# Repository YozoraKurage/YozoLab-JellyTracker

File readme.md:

# Yozolab-JellyTracker

### ✨️現在作成中です！✨️

私の作った[SlimeVR](https://github.com/SlimeVR)トラッカーに関するリポジトリです。

## FW書き込みについて(書き途中です)
JellyTrackerを私から購入した場合、WebページからFWの更新ができます \
https://jt-webflash.yozolab.net/

## 動作確認済みデータ
- [x] JellyTracker_V0.2.0
- [x] JellyTracker_V0.5.0
- [x] LSM_Module_V0.1.0
- [x] Ni-MH_3.3V-Module_V0.1.0

## KiCADデータについて
(今のところ)すべてKiCAD 7.0で作成されています\
私の導入しているプラグイン
- Espressif Library
- KiCAD JLCPCB tools

## JT_V0.5.0

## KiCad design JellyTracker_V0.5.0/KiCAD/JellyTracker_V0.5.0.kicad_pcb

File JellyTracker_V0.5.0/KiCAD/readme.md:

# JellyTracker_V0.5.0 KiCADデータ

> [!NOTE]
> このKiCADデータはKiCAD V7.0で作成されました！

AUXトラッカーとして、LSM_Module-V0.1.0が利用可能です
> LSM_ModuleとNi-MH_3.3V-Moduleを利用してNi-MH一本での運用が可能です。\
> JT_V0.5.0はそのために作成されました

## How to Upload to JLCPCB
jlcpcb/production_filesに出力されたBOM、CPL、GERBERデータがあるので、それを使うかKiCADからデータを作成してください

## Parts list

| What's it? | Parts Name | LCSC No. |
| ---- | ---- | ---- |
| TypeC Connector | TYPE-C-31-M-12 | C165948 |
| ESP32C3 Module | ESP32-C3-WROOM-02-N4 | C2934560 |
| 3.3V Regulator | ME6211C33M5G-N | C82942 |
| PushButton | SKRKAEE020 | C115357 |
| Caps | CL21B105KBFNNNE | C28323 |
| Resistor | 0603WAF5101T5E  | C23186 |
| Resistor | 0603WAF1002T5E  | C25804 |
| Diode | CUS10S30,H3F | C146335 |
| PH 2.0 | PH-4P | C50137 |

> [!IMPORTANT]
> 私のPH2.0ケーブルでは、必ず **SameSide** のケーブルを使う必要があります！

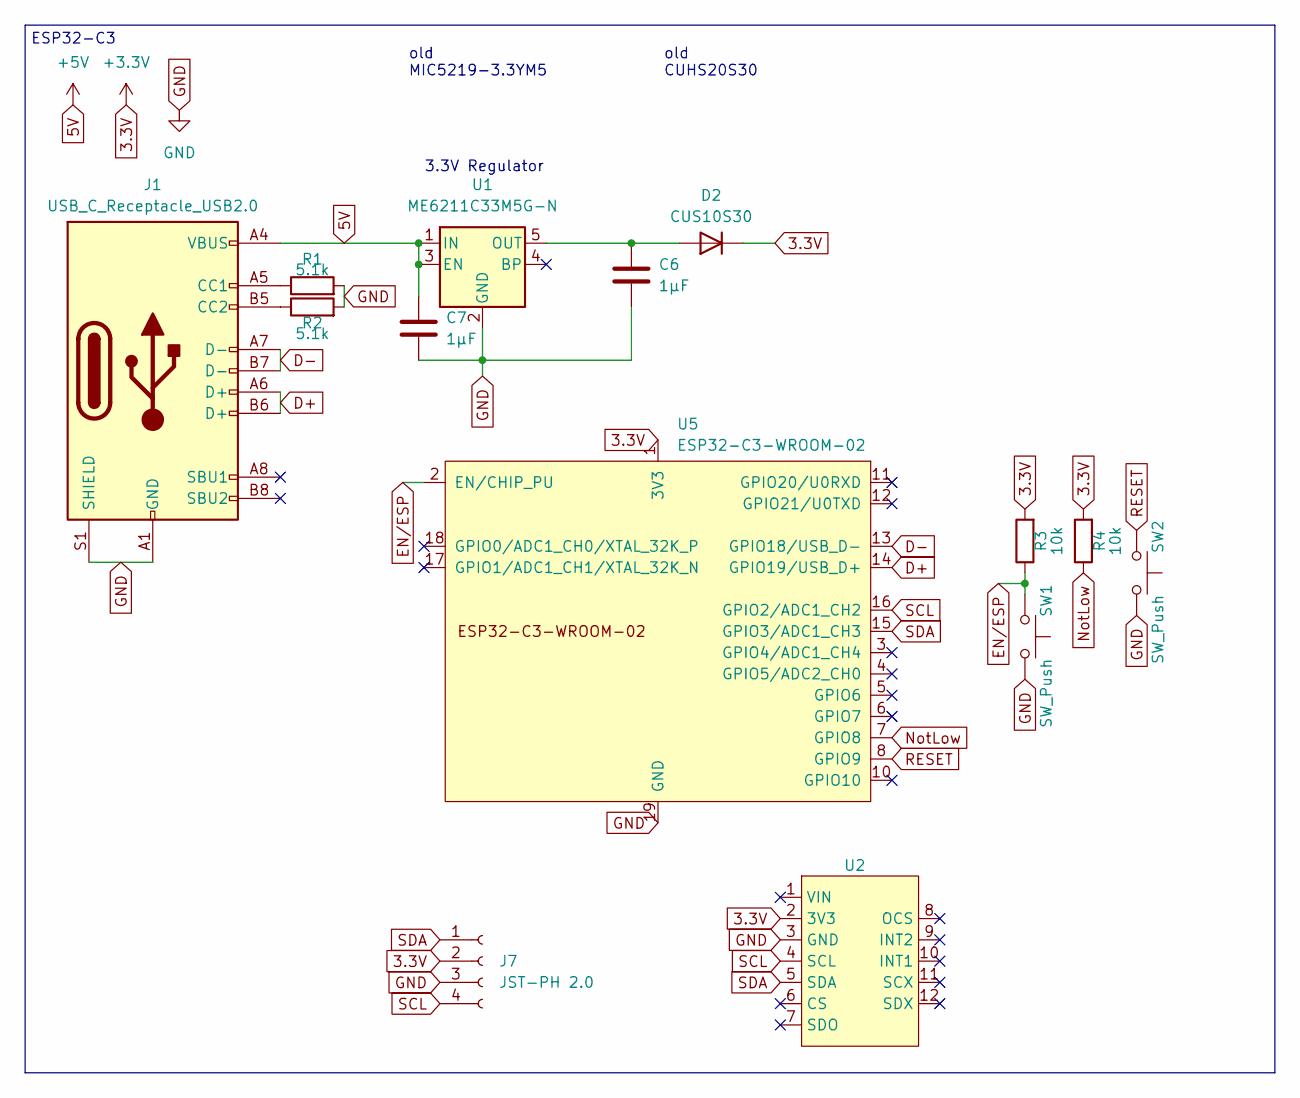
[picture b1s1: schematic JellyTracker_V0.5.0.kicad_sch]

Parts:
C6, C7: 1μF; C_0805_2012Metric
D2: CUS10S30; D_SOD-323
J1: USB_C_Receptacle_USB2.0; USB_C_Receptacle_HRO_TYPE-C-31-M-12
J7: JST-PH 2.0; JST_PH_S4B-PH-SM4-TB_1x04-1MP_P2.00mm_Horizontal
R1, R2: 5.1k; R_0603_1608Metric
R3, R4: 10k; R_0603_1608Metric
SW1, SW2: SW_Push; SW_Push_SPST_NO_Alps_SKRK
U1: ME6211C33M5G-N; SOT-23-5
U2: BMI160-Module
U5: ESP32-C3-WROOM-02

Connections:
3.3V: D2.1 (K), J7.2, R3.2, R4.2, U2.2 (3V3), U5.1 (3V3)
5V: C7.2, J1.A4 (VBUS), J1.A9 (VBUS), J1.B4 (VBUS), J1.B9 (VBUS), U1.1 (IN), U1.3 (EN)
D+: J1.A6 (D+), J1.B6 (D+), U5.14 (GPIO19/USB_D+)
D-: J1.A7 (D-), J1.B7 (D-), U5.13 (GPIO18/USB_D-)
EN/ESP: R3.1, SW1.1, U5.2 (EN/CHIP_PU)
GND: C6.2, C7.1, J1.A1 (GND), J1.A12 (GND), J1.B1 (GND), J1.B12 (GND), J1.S1 (SHIELD), J7.3, R1.2, R2.2, SW1.2, SW2.2, U1.2 (GND), U2.3 (GND), U5.9 (GND), U5.19 (GND)
unnamed: C6.1, D2.2 (A), U1.5 (OUT)
unnamed: J1.A5 (CC1), R1.1
unnamed: J1.B5 (CC2), R2.1
NotLow: R4.1, U5.7 (GPIO8)
RESET: SW2.1, U5.8 (GPIO9)
SCL: J7.4, U2.4 (SCL), U5.16 (GPIO2/ADC1_CH2)
SDA: J7.1, U2.5 (SDA), U5.15 (GPIO3/ADC1_CH3)

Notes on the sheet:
ESP32-C3
old CUHS20S30
3.3V Regulator
old MIC5219-3.3YM5

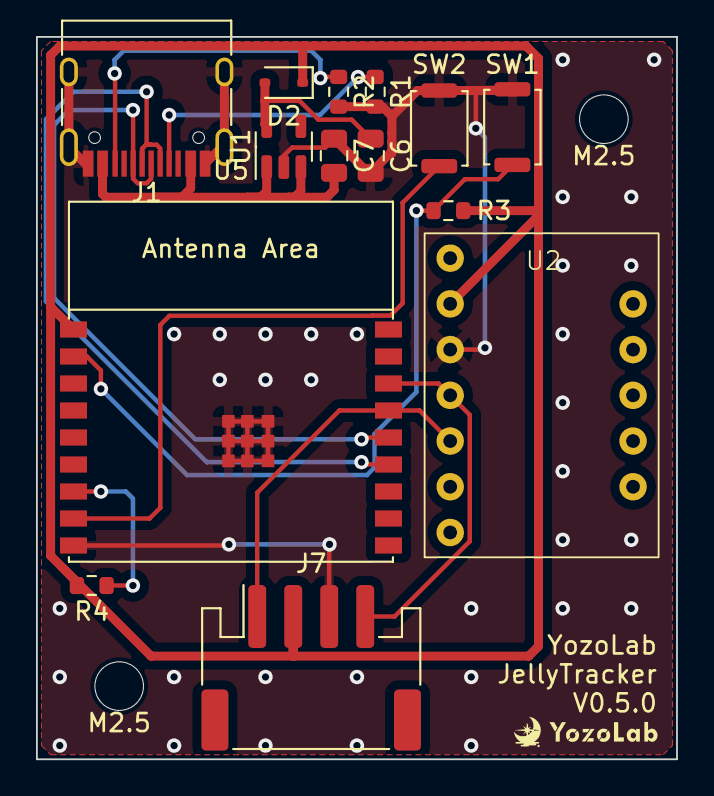
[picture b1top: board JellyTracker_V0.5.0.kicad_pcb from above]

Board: 2 copper layers, 35.6 x 40.1 mm, 16 parts (0 on the bottom side), 13 nets.

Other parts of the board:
M2.5, M2.5#2: MountingHole_2.7mm_M2.5

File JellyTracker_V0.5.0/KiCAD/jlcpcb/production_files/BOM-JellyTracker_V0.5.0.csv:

Comment,Designator,Footprint,LCSC,Quantity
SW_Push,"SW1,SW2",SW_Push_SPST_NO_Alps_SKRK,C115357,2
"CUS10S30
",D2,D_SOD-323,C146335,1
USB_C_Receptacle_USB2.0,J1,USB_C_Receptacle_HRO_TYPE-C-31-M-12,C165948,1
5.1k,"R1,R2",R_0603_1608Metric,C23186,2
10k,"R3,R4",R_0603_1608Metric,C25804,2
1μF,"C6,C7",C_0805_2012Metric,C28323,2
ESP32-C3-WROOM-02,U5,ESP32-C3-WROOM-02,C2934560,1
JST-PH 2.0,J7,JST_PH_S4B-PH-SM4-TB_1x04-1MP_P2.00mm_Horizontal,C50137,1
ME6211C33M5G-N,U1,SOT-23-5,C82942,1

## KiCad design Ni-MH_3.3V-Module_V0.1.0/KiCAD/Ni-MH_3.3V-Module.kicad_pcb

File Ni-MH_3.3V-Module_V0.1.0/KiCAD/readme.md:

# NiMH 3.3V昇圧モジュール KiCADデータ
Ni-MHを3.3Vへ昇圧するモジュールです。

## How to Upload to JLCPCB
jlcpcb/production_filesに出力されたBOM、CPL、GERBERデータがあるので、それを使うかKiCADからデータを作成してください

## Parts list
| What's it? | Parts Name | LCSC No. |
| ---- | ---- | ---- |
| Caps | CL10C100JB8NNNC | C1634 |
| Inductor | DFE252012P-R47M=P2 | C237552 |
| Resistor | 0603WAF3163T5E | C25814 |
| 1.2v to 3.3v DCDC | TPS61021ADSGR | C193037 |
| Caps | CL21A226MAQNNNE  | C45783 |
| Resistor | 0603WAF1003T5E | C25803 |
| Diode | CUS10S30,H3F | C146335 |

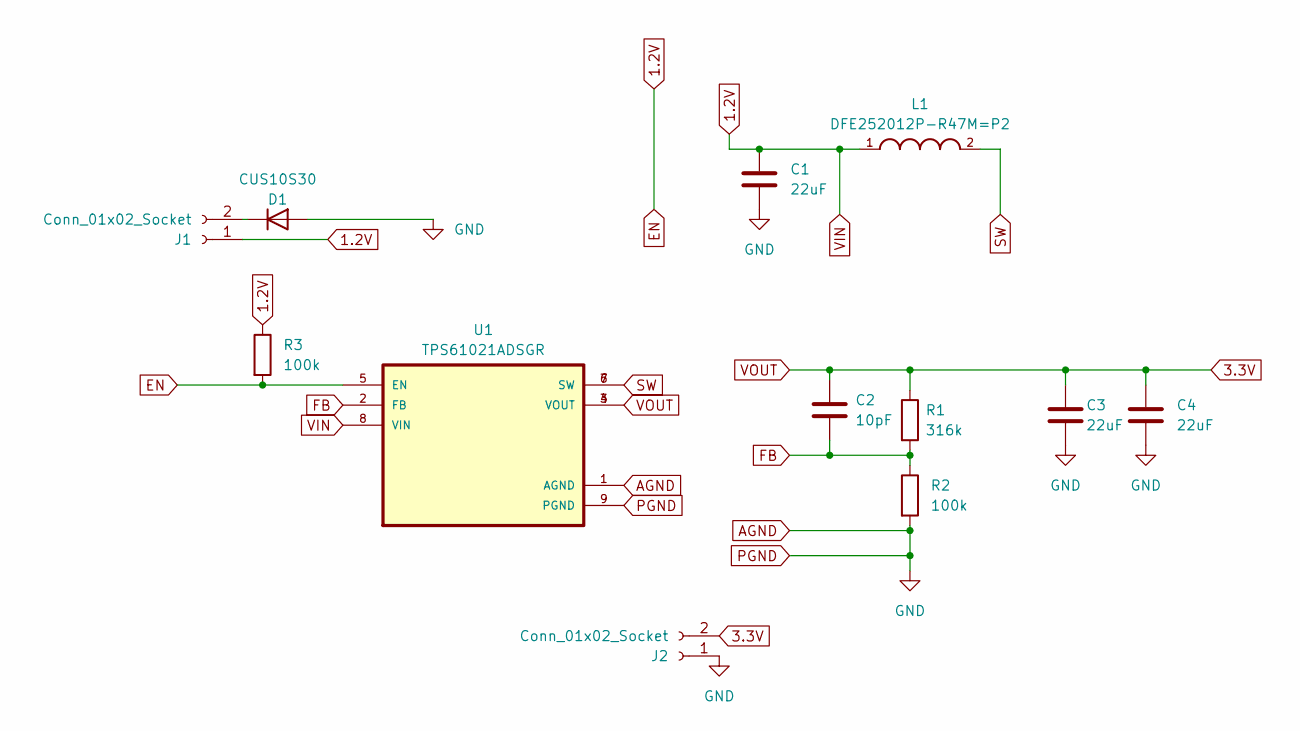
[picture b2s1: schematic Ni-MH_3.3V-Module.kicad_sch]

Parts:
C1, C3, C4: 22uF; C_0805_2012Metric
C2: 10pF; C_0603_1608Metric
D1: CUS10S30; D_SOD-323
J1, J2: Conn_01x02_Socket; Through-Hole
L1: DFE252012P-R47M=P2; INDC2520X120N
R1: 316k; R_0603_1608Metric
R2, R3: 100k; R_0603_1608Metric
U1: TPS61021ADSGR; SON50P200X200X80-9N

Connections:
1.2V: C1.2, J1.1, L1.1, R3.1, R3.2, U1.5 (EN), U1.8 (VIN)
3.3V: C2.2, C3.2, C4.2, J2.2, R1.1, U1.3 (VOUT), U1.4 (VOUT)
AGND: C1.1, C3.1, C4.1, D1.2 (A), J2.1, R2.2, U1.1 (AGND), U1.9 (PGND)
FB: C2.1, R1.2, R2.1, U1.2 (FB)
unnamed: D1.1 (K), J1.2
SW: L1.2, U1.6 (SW), U1.7 (SW)

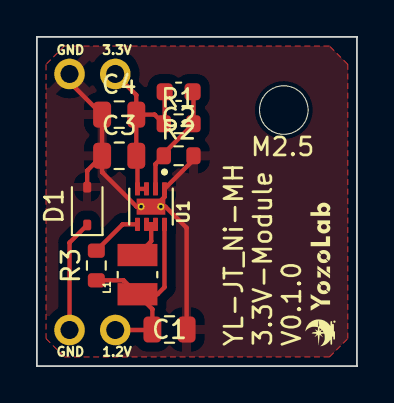
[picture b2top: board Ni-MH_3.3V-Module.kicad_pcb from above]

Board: 2 copper layers, 17.8 x 18.3 mm, 13 parts (0 on the bottom side), 6 nets.

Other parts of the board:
M2.5: MountingHole_2.7mm_M2.5

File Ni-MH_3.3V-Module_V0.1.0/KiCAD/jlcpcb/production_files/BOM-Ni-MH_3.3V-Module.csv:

Comment,Designator,Footprint,LCSC,Quantity
CUS10S30,D1,D_SOD-323,C146335,1
10pF,C2,C_0603_1608Metric,C1634,1
TPS61021ADSGR,U1,SON50P200X200X80-9N,C193037,1
DFE252012P-R47M=P2,L1,INDC2520X120N,C237552,1
100k,"R2,R3",R_0603_1608Metric,C25803,2
316k,R1,R_0603_1608Metric,C25814,1
22uF,"C1,C3,C4",C_0805_2012Metric,C45783,3

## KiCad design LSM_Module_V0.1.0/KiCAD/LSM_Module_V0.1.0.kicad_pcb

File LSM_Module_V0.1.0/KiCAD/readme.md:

# LSM_Module_V0.1.0 KiCADデータ

LSM6シリーズ、及びBMIシリーズのモジュールにコネクタを付けてAUXトラッカーとして扱うための基板データです。

白猫屋さんのこのLSM6DSVモジュールでの動作を確認済みです。\
https://booth.pm/ja/items/5606882

## How to Upload to JLCPCB
jlcpcb/production_filesに出力されたBOM、CPL、GERBERデータがあるので、それを使うかKiCADからデータを作成してください

## Parts list
| Parts Name | LCSC No. |
| ---- | ---- |
| PH2.0mm 4pin | C50137 or https://www.aliexpress.com/item/1005006027334406.html |
| PH2.0mm 4pin-wire **SameSide** | https://ja.aliexpress.com/item/1005003395992629.html |

> [!IMPORTANT]
> 私のPH2.0ケーブルでは、必ず **SameSide** のケーブルを使う必要があります！

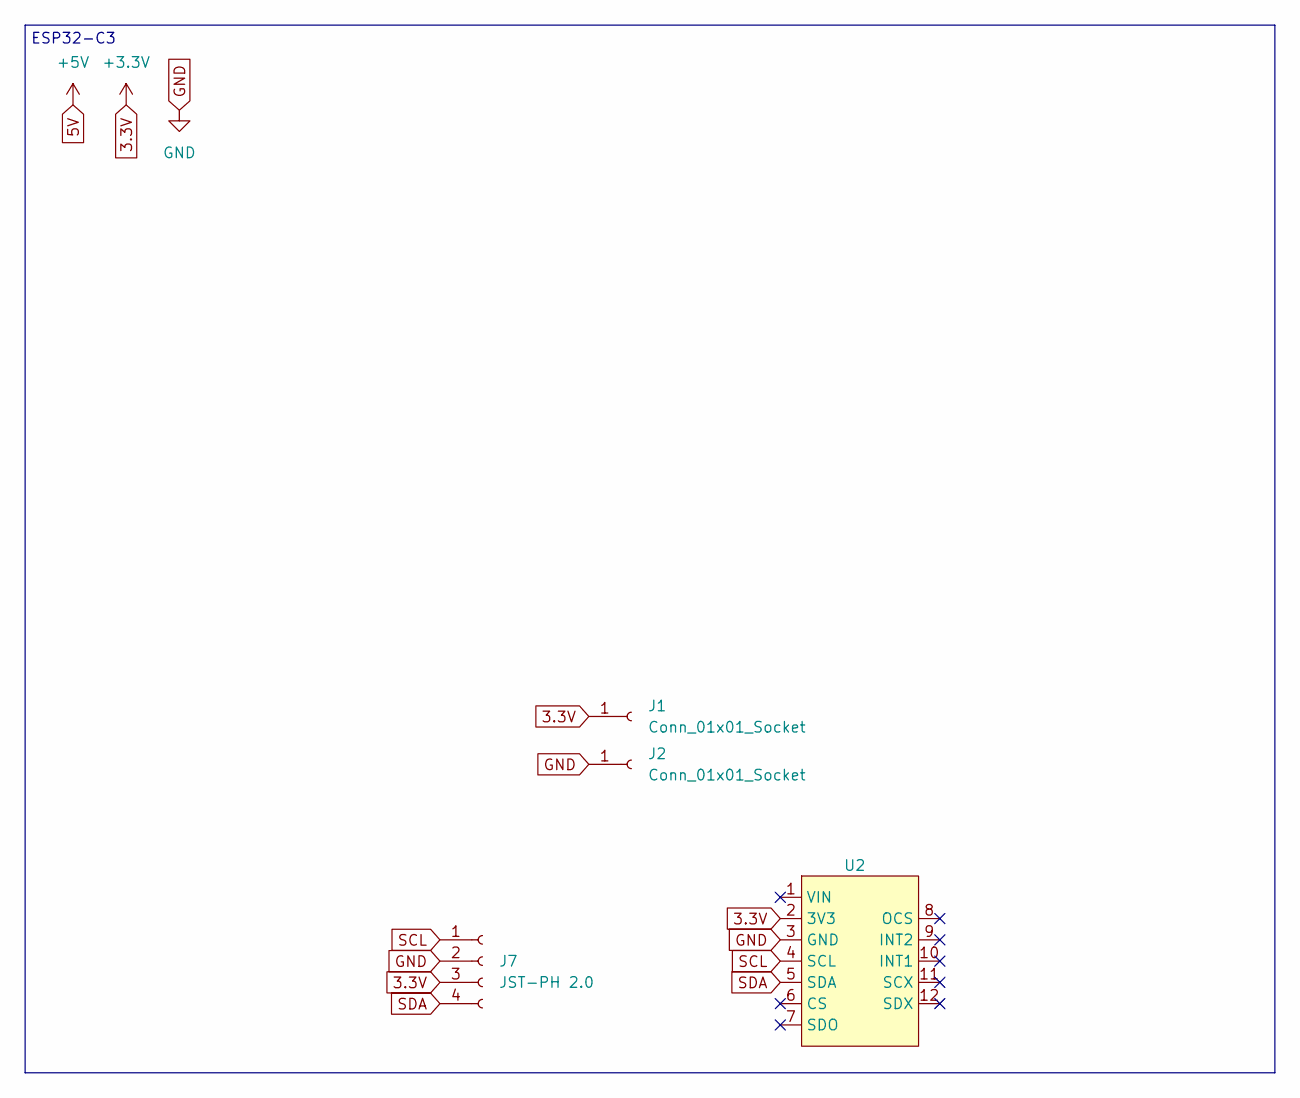
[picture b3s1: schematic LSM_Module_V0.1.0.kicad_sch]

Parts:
J1, J2: Conn_01x01_Socket; Through-Hole
J7: JST-PH 2.0; JST_PH_S4B-PH-SM4-TB_1x04-1MP_P2.00mm_Horizontal
U2: BMI160-Module

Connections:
3.3V: J1.1, J7.3, U2.2 (3V3)
GND: J2.1, J7.2, U2.3 (GND)
SCL: J7.1, U2.4 (SCL)
SDA: J7.4, U2.5 (SDA)

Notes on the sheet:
ESP32-C3

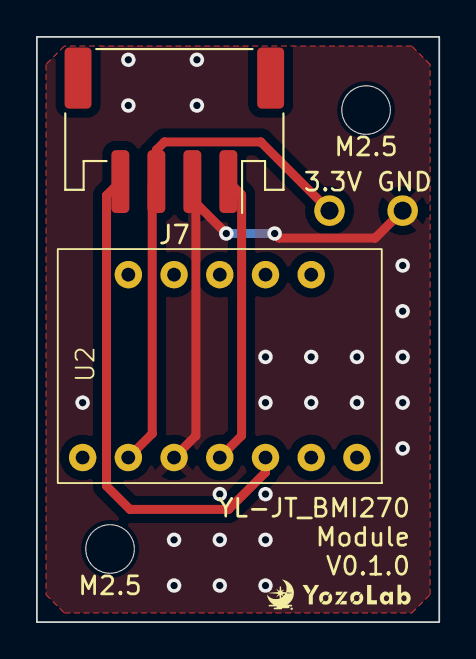
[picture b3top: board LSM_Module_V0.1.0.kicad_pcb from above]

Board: 2 copper layers, 22.4 x 32.5 mm, 6 parts (0 on the bottom side), 4 nets.

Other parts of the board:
M2.5, M2.5#2: MountingHole_2.7mm_M2.5

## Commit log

2024-11-10 meow
2024-11-11 gitignore
2024-11-11 vscode d ignore
2024-11-11 add about fw
